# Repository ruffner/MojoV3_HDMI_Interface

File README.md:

# Dual HDMI + Camera Interface PCB for 120Hz SLI

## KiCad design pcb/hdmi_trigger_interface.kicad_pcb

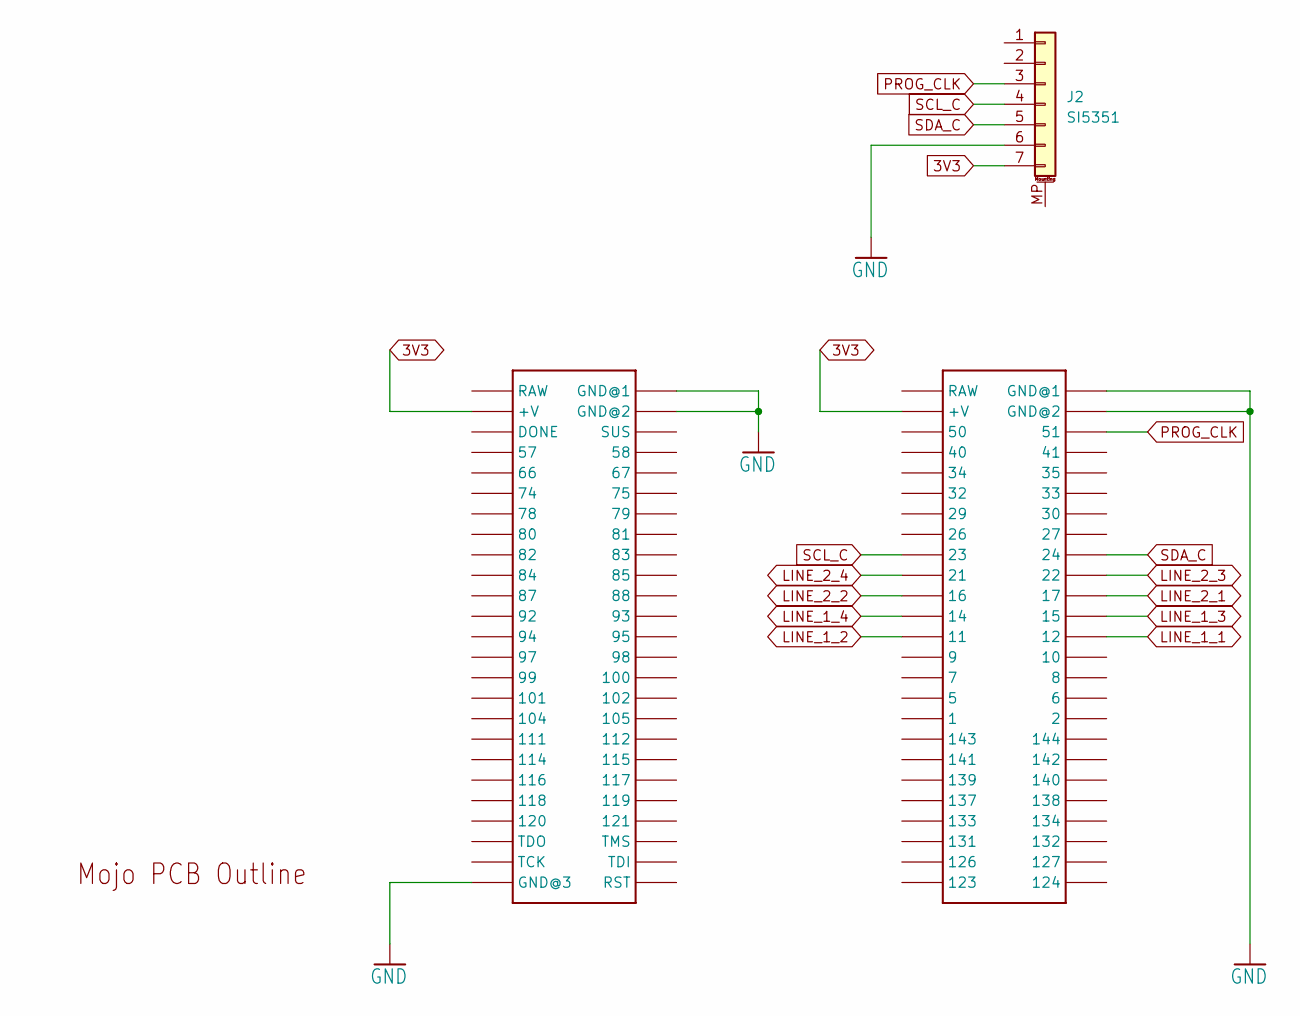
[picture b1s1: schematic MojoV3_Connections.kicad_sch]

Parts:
J2: SI5351; PinHeader_1x07_P2.54mm_Vertical
U$1: MOJOV3; MOJO_V3
U$2: MOJO_OUTLINE

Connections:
3V3: J2.7, U$1.V@1 (+V), U$1.V@2 (+V); also elsewhere on the board
5V: U$1.RAW@1 (RAW), U$1.RAW@2 (RAW)
CLK1_N: U$1.143
CLK1_P: U$1.144
CLK2_N: U$1.120
CLK2_P: U$1.121
CTHPD1: U$1.7
CTHPD2: U$1.102
D01_N: U$1.141
D01_P: U$1.142
D02_N: U$1.118
D02_P: U$1.119
D11_N: U$1.139
D11_P: U$1.140
D12_N: U$1.116
D12_P: U$1.117
D21_N: U$1.137
D21_P: U$1.138
D22_N: U$1.114
D22_P: U$1.115
GND: J2.6, U$1.GND@1, U$1.GND@2, U$1.GND@3 (GND@1), U$1.GND@4 (GND@2), U$1.GND@6 (GND@3); also elsewhere on the board
HP1_M: U$1.5
HP2_M: U$1.100
LINE_1_1: U$1.12; also elsewhere on the board
LINE_1_2: U$1.11; also elsewhere on the board
LINE_1_3: U$1.15; also elsewhere on the board
LINE_1_4: U$1.14; also elsewhere on the board
LINE_2_1: U$1.17; also elsewhere on the board
LINE_2_2: U$1.16; also elsewhere on the board
LINE_2_3: U$1.22; also elsewhere on the board
LINE_2_4: U$1.21; also elsewhere on the board
PROG_CLK: J2.3, U$1.51
SCL1_M: U$1.1
SCL2_M: U$1.95
SCL_C: J2.4, U$1.23
SDA1_M: U$1.2
SDA2_M: U$1.98
SDA_C: J2.5, U$1.24

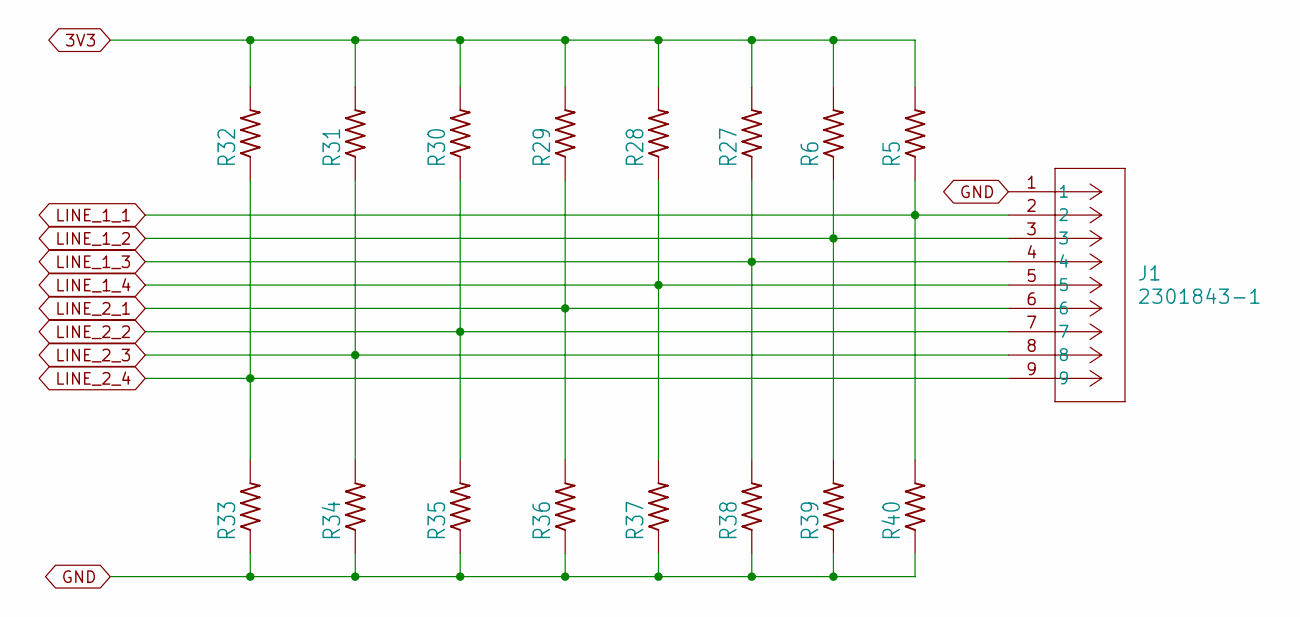
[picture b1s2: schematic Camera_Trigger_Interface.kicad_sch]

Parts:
J1: 2301843-1; CONN9X1_2286550-1_TEC
R5, R6, R27, R28, R29, R30, R31, R32, R33, R34, R35, R36, R37, R38, R39, R40: R-US_R0603; R_Axial_DIN0207_L6.3mm_D2.5mm_P10.16mm_Horizontal

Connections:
3V3: R5.2, R6.2, R27.2, R28.2, R29.2, R30.2, R31.2, R32.2; also elsewhere on the board
GND: J1.1, R33.1, R34.1, R35.1, R36.1, R37.1, R38.1, R39.1, R40.1; also elsewhere on the board
LINE_1_1: J1.2, R5.1, R40.2; also elsewhere on the board
LINE_1_2: J1.3, R6.1, R39.2; also elsewhere on the board
LINE_1_3: J1.4, R27.1, R38.2; also elsewhere on the board
LINE_1_4: J1.5, R28.1, R37.2; also elsewhere on the board
LINE_2_1: J1.6, R29.1, R36.2; also elsewhere on the board
LINE_2_2: J1.7, R30.1, R35.2; also elsewhere on the board
LINE_2_3: J1.8, R31.1, R34.2; also elsewhere on the board
LINE_2_4: J1.9, R32.1, R33.2; also elsewhere on the board

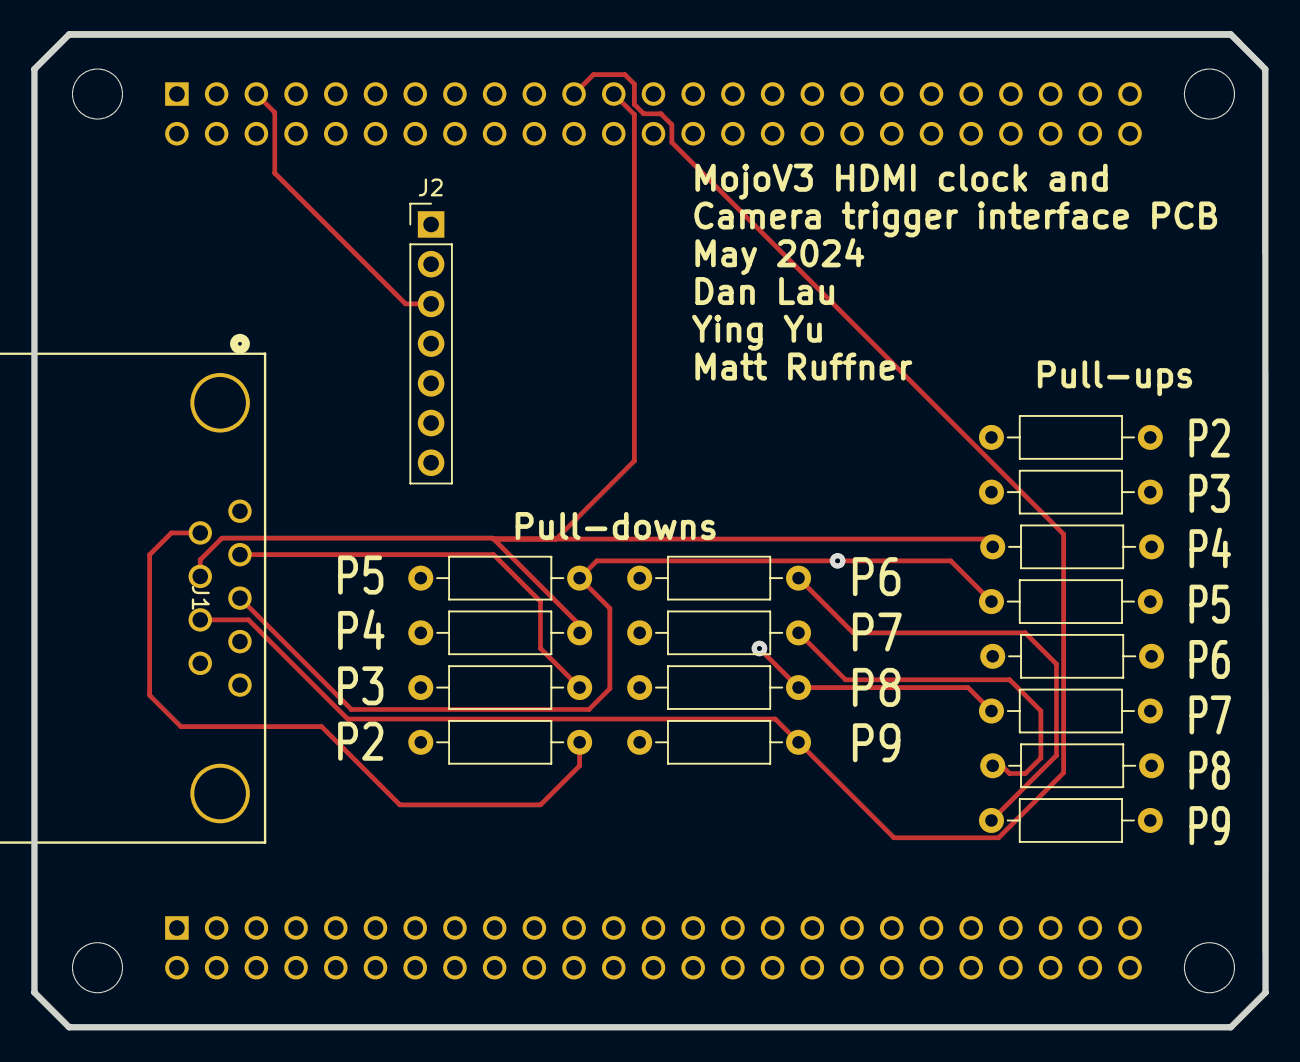
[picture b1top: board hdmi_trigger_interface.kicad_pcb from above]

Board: 4 copper layers, 78.7 x 63.5 mm, 19 parts (0 on the bottom side), 14 nets.

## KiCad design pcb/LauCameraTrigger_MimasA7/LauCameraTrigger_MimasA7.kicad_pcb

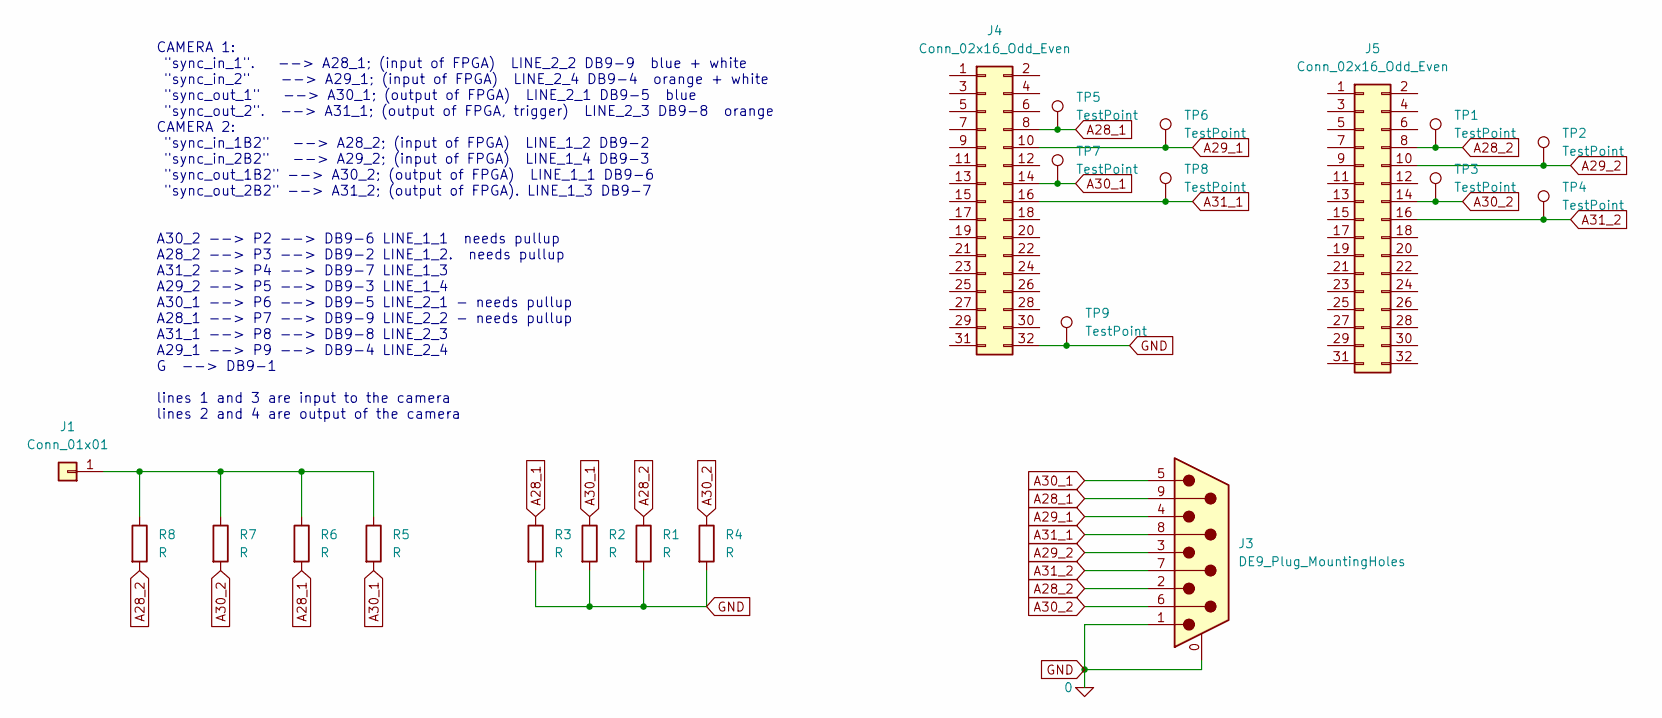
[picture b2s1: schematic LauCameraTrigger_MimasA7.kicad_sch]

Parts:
J1: Conn_01x01; Pin_D1.3mm_L11.0mm
J3: DE9_Plug_MountingHoles; DSUB-9_Male_Horizontal_P2.77x2.84mm_EdgePinOffset4.94mm_Hou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
J4, J5: Conn_02x16_Odd_Even; PinHeader_2x16_P2.54mm_Vertical
R1, R2, R3, R4, R5, R6, R7, R8: R; R_Axial_DIN0207_L6.3mm_D2.5mm_P10.16mm_Horizontal
TP1, TP2, TP3, TP4, TP5, TP6, TP7, TP8, TP9: TestPoint; TestPoint_Pad_D2.0mm

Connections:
A28_1: J3.9, J4.8, R3.1, R6.2, TP5.1
A28_2: J3.2, J5.8, R1.1, R8.2, TP1.1
A29_1: J3.4, J4.10, TP6.1
A29_2: J3.3, J5.10, TP2.1
A30_1: J3.5, J4.14, R2.1, R5.2, TP7.1
A30_2: J3.6, J5.14, R4.1, R7.2, TP3.1
A31_1: J3.8, J4.16, TP8.1
A31_2: J3.7, J5.16, TP4.1
GND: J3.0 (PAD), J3.1, J4.32, R1.2, R2.2, R3.2, R4.2, TP9.1
unnamed: J1.1, R5.1, R6.1, R7.1, R8.1

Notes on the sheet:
CAMERA 1: "sync_in_1". --> A28_1; (input of FPGA) LINE_2_2 DB9-9 blue + white "sync_in_2" --> A29_1; (input of FPGA) LINE_2_4 DB9-4 orange + white "sync_out_1" --> A30_1; (output of FPGA) LINE_2_1 DB9-5 blue "sync_out_2". --> A31_1; (output of FPGA, trigger) LINE_2_3 DB9-8 orange CAMERA 2: "sync_in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

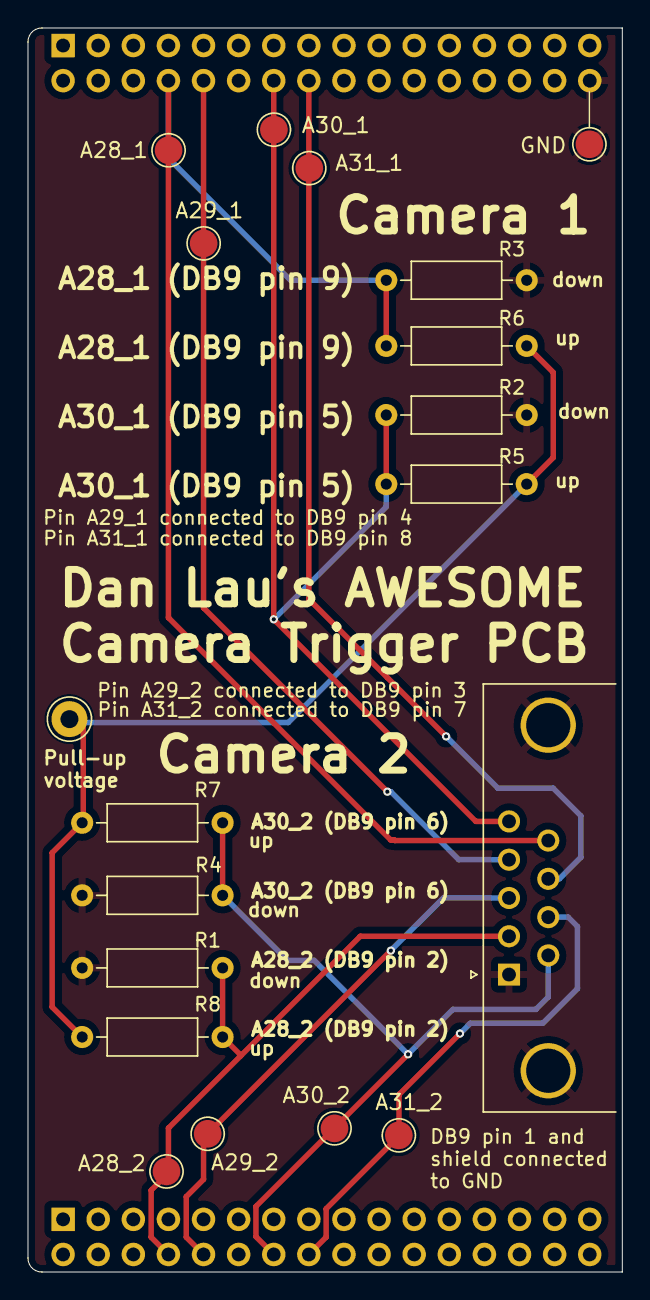
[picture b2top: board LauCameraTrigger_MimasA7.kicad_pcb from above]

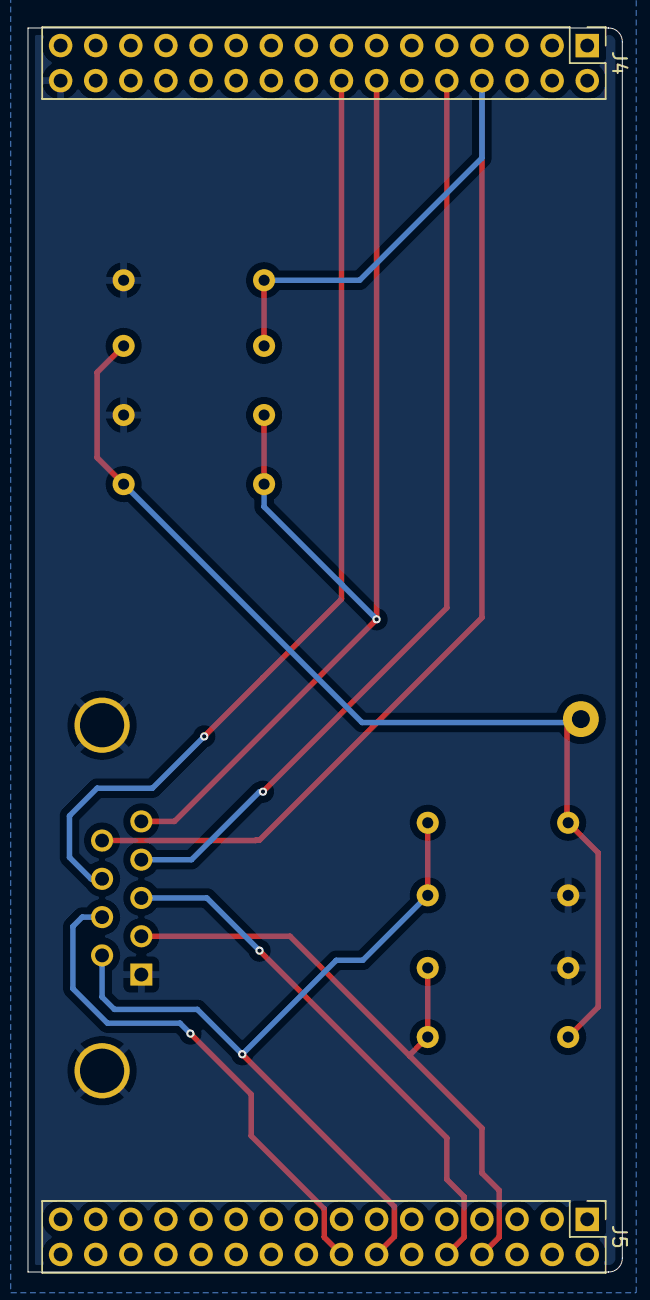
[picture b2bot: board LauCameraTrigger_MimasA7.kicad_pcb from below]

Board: 2 copper layers, 43.0 x 90.0 mm, 21 parts (2 on the bottom side), 10 nets.

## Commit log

2019-01-21 initial commit with pcb outline and html5 up template
2019-01-21 work on hdmi integration into basler trigger circuitry
2019-01-22 almost done with routing
2019-01-23 board layout 90% done, need parts list then will order
2019-01-24 added images from manufacturing render and gerbers sent to pcbway
2019-02-12 rerouting with a 4 layer board and 7.6mil traces and 6mil spacing for 100 ohm differential impedance' g
2019-02-12 more routing
2019-02-13 hdmi differential pairs routed and length tunedgit status
2019-02-13 spacing tweaks
2019-02-14 length tuning and routing done, need final review then ready to order
2019-02-14 final tweaks
2019-02-28 added .gitignore file
2019-02-28 added conn library
2019-03-01 ripped up old diff pairs, ready to route new 8/8 lines
2019-03-05 one hdmi port routed, one to go. net class made with 8/8 mil trace width and spacing
2019-03-05 started routing second hdmi port
2019-03-06 work on routing second hdmi port
2019-03-18 more work on length tuning
2019-03-20 finished routing with new spacing and layout.
2019-03-20 final tweak
2019-03-20 added previous and current gerbers
2019-03-20 added 4 layer pcbway cam file
2019-03-20 removed desktop.ini
2019-05-29 added power supply mount
2025-01-01 add DB9 MOJO shield and DB9 Numato shield
2025-01-01 remove web docs
